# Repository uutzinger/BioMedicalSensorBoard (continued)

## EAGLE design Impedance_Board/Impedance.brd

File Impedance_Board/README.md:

# Tissue Impedance

IEC 60601 limits 100 µA maximum dc-leakage current through the body under normal conditions and 500 µA maximum under worst-case, single-fault conditions. An impedance circuit should not exceed that current.

## Analog Front Ends
### Analog Devices
- [AD5933 12-bit impedance converter ($18)](https://www.analog.com/en/products/ad5933.html) evaluation kit available ($68)
- [User Guide with reference schematics](https://www.analog.com/media/en/technical-documentation/user-guides/UG-364.pdf)

### Maxim AFE
- Biopotential
  - ECG (waveform)
  - R-R (heart rate)
- Bioimpedance
  - Resp (respiration)
  - GSR (galvanic skin response, stress level)
  - EDA (electro dermal activity)

- [Max 30001G ($10)](https://www.maximintegrated.com/en/products/analog/data-converters/analog-front-end-ics/MAX30001G.html) for Biopotential and Bioimpedance, evaluation kit available ($113)
- [Maxim 30009](https://www.maximintegrated.com/en/products/sensors/MAX30009.html) for Bioimpedance, evaluation kit available ($212)

### Summary of AFEs
| PART | Features             | Resolution | Remarks |
|---   |---                   |---         |---      |
| AD5933    | Single channel 3 wire | 12bit, 1Msps, 100kHz excitation| First Gen, 1024 point FFT, 1kOhm - 1MOhm
| AD5940/41 | 2 channel, 4 wire | 16bit, 800ksps, 200kHz | Impedance spectroscopy
| ADuC355   | 2 channel, 4 wire | 16bit, 800ksps, 200kHz | Impedance Spectroscopy, 26MHz ARM Cortex M3 MCU
| MAX30002  | single channel, BioZ, 2 or 4 wire | 17bit| 
| MAX30009  | single channel, BioZ, 2 or 4 wire | 16 kHz - 806 kHz |
| MAX30131/132/134 | 1-,2-,4- channel | 12 bit |
| MAX30001G | single channel, 2 or 4 wire | | Impedance and Potential (ECG)

## AD5933 for Bioimpedance

The AD5933 is a network analyzer IC that together with external circuitry can be used for bioimpedance measurements.

From [1] and [2], made with https://www.circuit-diagram.org/editor

### AD5933 Evaluation Board

The evaluation board from Analog Devices includes the reference design describing an analog front end to measure low impedances.

On the excitation side it has a passive high pass filter with $R_{HP}$, $C_{HP}$ and an OpAmp buffer.

On the measurement side it has an amplifier with $V_{DD}/2$ on the positive input and feedback resistor RFB.

The input to the AD5933 has $R_{AD_{IN}}$ of 20K as well as a $R_{AD_{FB}}$ of 20K.

### USING AD5933 for Bioimpedance Measurements

Munoz et al [2] describe their implementation in a 2022 paper. Several other web publications exist using that design.

For bioimpedance measurements the following analog front end elements should be used: a high-pass filter (HPF), a voltage-to-current converter (VCC), and an instrumentation amplifier (INA).

The HPF is a first order system composed of a 100 kΩ resistor and a 10 nF capacitor to remove the DC components of $V_{out}$. $f_c = 1 / (2 \pi R C)$ resulting in 160Hz. 

The HPF output is connected to VCC, which consists of an operational amplifier and two resistors. The current injected into the tissue should not exceed 10 uA. 

$R_{VCC current} = 1 kΩ$ (This will exceed 10 µA!)

$R_{VCC_{protect}} = 10 kΩ$

Because the impedance is supposed to vary from tens to hundreds of ohms, 

$R_{feedback} = 10 kΩ$ 

ensures that current flows mainly through $Z_{Load}$, which is connected in parallel to $R_{feedback}$.

The current through VCC is

$R_{VCC_{curent}} = (V_{out} - V_{ref}) / R_{VCC_{current}}$. 

Therefore the voltage over $Z_{load}$ is

$V_{Z_{load}} = -(V_{out} - V_{ref}) / R_{VCC_{current}} * Z_{load}$.

The unity gain instrumentation amplifier receives, through its non-inverting input, the voltages on the electrodes connected to $Z_{load}$. Since the ADC converter of the AD5933 is unipolar, a potential ($V_{ref}$) is added as reference voltage to the instrumentation amplifier. The output of the INA is 

$V_{INA} =  V_{load} + V_{ref}

The current through $R_{AD_{IN}}$ is:

$(V_{INA} - V_{ref})/R_{AD_{IN}}$

The output of the internal OpAmp in the AD5933 is 

$I_{RFB} * R_{AD_{FB}}$

Therefore 

$V_{AD5933} = (V_{INA} - V_{ref})/R_{AD{IN}} * R_{AD_{FB}}$.

The DSP of the AD5933 calculates the real and imaginary parts of $Z_{load}$, which are read through an inter-integrated circuit (I2C) protocol by a micro controller.

### External Electrical Components for AD5933

A list of designs using the AD5933 used the following values for resistors and capacitors:

| Design        | $C_{HP}$ | $R_{HP}$ | $RFB$ | $R_{VCC_{current}}$ | $R_{VCC_{protect}}$ | $R_{INA_{GAIN}}$ | $R_{REFGEN}$ | $R_{AD_{IN}}$ | $R_{AD_{FB}}$ | $VCC +$
|---            |---   |---    |---   |---            |---              |---            |---       |---      |---      |---
| Eval [1]      | 47nF | 49.9k | 200k | N.A.          | N.A.            | N.A.          | 49.9k    | 20k     | 20k     |
| Datasheet [3] | 47nF | N.S.  | N.S. | N.A.          | N.A.            | N.A.          | N.S.     | 20k     | 20k     |
| Munoz [2]     | 10nF | 100k  | N.A. | 1k            | 10k             | Gain=1        | 1k       | 1k      | 1k      | GND
| Instru Bio [4]| 10nF |  10k  | N.A. | 1k            |  1k             | Gain=10,5.5k  | VDD/2    | 1k      | 1k      | GND
| Instru BIA [5]| 10nF | 100k  | N.A. | 1M            |  1M             | Gain=1.5,100k | VDD/2    | 1k      | 1k      | GND
| Instru BIA [6]| 10nF | 100k  | N.A. | 285k          |  1M             |               | VDD/2    |         |         | VDD/2
| Instru Thor[7]| 1.2nF|  10k  | N.A. | 1M            |  1M             | Gain=1.5,100k | 1k       | 1k      | 1k      | GND
| Instru Thor[8]| 100nF|  20k  | N.A. | 100k          |  10k            | Gain=1.5,100k | 3.2/1k   | 1k      | 1k      | GND
| UA 2023       | 10nF | 100k  | N.A. |  82k          |  82k            | Gain=51,1k    | 20k      | 20k     | 20k     | VDD/2
| UA 2024       | 10nF | 100k  | 200k | 265k          |   1k            | Gain=51,1k    | 10k      | 20k     | 20k     | VDD/2

Common active components used for AD5933 biomimpedance:
- Network Analyzer AD5933
- Operation Amplifier(s) AD8608 or AD8606 or AD8605
- Instrumentation Amplifier INA826AID

#### High Pass
- $1 / (2 \pi R C)$, should attenuate 50 and 60Hz, need 200Hz..xxkHz
- 10nF, 100k fc=160Hz

#### $R_{current}$ and $R_{protect}$
- Input into VCC is at 1.65V offset with 1V amplitude. With $I_{CC} <10uA$ and $V_{CC} = 2.65V$ and $R_{VCC_{current}}$ will need to be 265kΩ.
- Setting of Range 1 in AD5933 is 1V if operating at 3.3V., for $10 \mu A$ we need 110kΩ for $R_{VCC_{current}}$.
- Analog Devices: "Bio-Impedance Circuit Design for Body Worn Systems"

#### $R_{Gain}$ 
- $G = 1 + (49.4k/R_{Gain})$
- With $R_{INA_{GAIN}}$  = 1kΩ the gain will be $G=51$

### Impedance Estimation

Formula to compute impedance from measurements: Description to be completed (check evaluation board and Instructables, also search PubMed).

### References

For general reading: [Analog Devices: Bio-Impedance Circuit Design for Body Worn Systems"](https://www.analog.com/en/resources/analog-dialogue/articles/bioimpedance-circuit-design-challenges.html)

1) [Analog Devices AD5933 Evaluation Board, User Guide](https://www.analog.com/media/en/technical-documentation/user-guides/UG-364.pdf)
2) [Munoz et al](https://doi.org/10.1016%2Fj.ohx.2022.e00274)
3) [AD5933 Datasheet](https://www.analog.com/media/en/technical-documentation/data-sheets/AD5933.pdf)
4) [Instructables Body Composition](https://www.instructables.com/Determining-Body-Composition-using-Arduino)
5) [Instructables BIA 1](https://www.instructables.com/Body-Composition-using-BIA/)
6) [Instructables BIA 2](https://www.instructables.com/Bio-Impedance-Analysis-BIA-With-the-AD5933/)
7) [Instructables Thor 1](https://www.instructables.com/Thoracic-Impedance-1/)
8) [Instructables THor 2](https://www.instructables.com/Thoracic-Impedance/)
9) [IEEE Tutorial](https://ieeexplore.ieee.org/document/9529213)
10) [Uwe Pliquett, Andreas Barthel, 2012 J. Phys.: Conf. Ser. 407 012019](https://iopscience.iop.org/article/10.1088/1742-6596/407/1/012019)
10) [Paco Bogonez-Franco et al, 2014, Problems encountered during inappropriate use of commercial bioimpedance devices in novel applications, 7 th International Workshop on Impedance Spectroscopy 2014](https://www.researchgate.net/publication/269571754_Problems_encountered_during_inappropriate_use_of_commercial_bioimpedance_devices_in_novel_applications)
12) [J Ferreira et al 2010 J. Phys.: Conf. Ser. 224 012011](https://iopscience.iop.org/article/10.1088/1742-6596/224/1/012011/pdf)

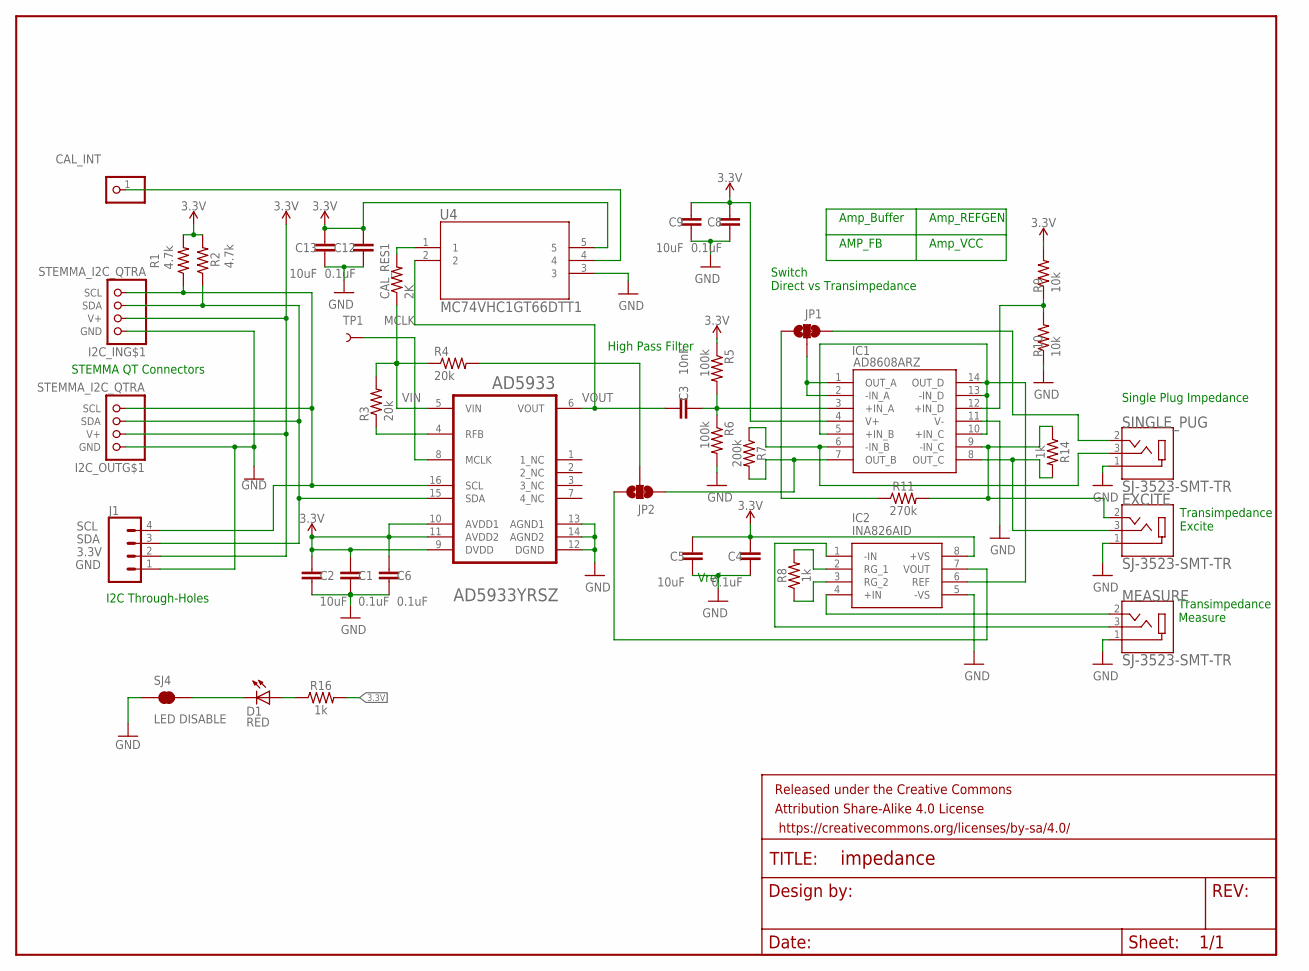
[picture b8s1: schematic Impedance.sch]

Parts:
AD5933: ANALOG_DEVICES_AD5933YRSZANALOG_DEVICES_AD5933YRS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; ANALOG_DEVICES_AD5933YRSZ_0
C1, C4, C6, C8, C12: 0.1uF; 0603
C2, C5, C9, C13: 10uF; 0603
C3: 10nF; 0603
CAL_INT: PINHD-1X1; 1X01
CAL_RES1: 2K; R0603
D1: RED; LED-0603
EXCITE: SJ-3523-SMT-TR; CUI_SJ-3523-SMT-TR
FRAME1: FRAME-LETTERNO_PACKAGE; DUMMY
I2C_IN, I2C_OUT: STEMMA_I2C_QTRA; JST_SH4_RA
IC1: AD8608ARZ; SOIC127P600X175-14N
IC2: INA826AID; SOIC127P600X175-8N
J1: CONN_04; 1X04
JP1, JP2: JUMPER-SMT_3_1-NC_TRACE_NO-SILK; SMT-JUMPER_3_1-NC_TRACE_NO-SILK
MEASURE: SJ-3523-SMT-TR; CUI_SJ-3523-SMT-TR
R1, R2: 4.7k; 0603
R3, R4: 20k; 0603
R5, R6: 100k; 0603
R7: 200k; 0603
R8, R14, R16: 1k; 0603
R9, R10: 10k; 0603
R11: 270k; 0603
SINGLE_PUG: SJ-3523-SMT-TR; CUI_SJ-3523-SMT-TR
SJ4: LED DISABLE; SMT-JUMPER_2_NC_TRACE_SILK
TP1: TEST-POINT3X5; PAD.03X.05
U4: MC74VHC1GT66DTT1; TSOP5_1P65X3P15_ONS

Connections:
3.3V: AD5933.9 (DVDD), AD5933.10 (AVDD1), AD5933.11 (AVDD2), C1.1, C2.1, C4.1, C5.1, C6.1, C8.1, C9.1, C12.1, C13.1, I2C_IN.2 (V+), I2C_OUT.2 (V+), IC1.4 (V+), IC2.8 (+VS), J1.2, R1.2, R2.2, R5.1, R9.2, R16.2, U4.5
GND: AD5933.12 (DGND), AD5933.13 (AGND1), AD5933.14 (AGND2), C1.2, C2.2, C4.2, C5.2, C6.2, C8.2, C9.2, C12.2, C13.2, EXCITE.1, I2C_IN.1 (GND), I2C_OUT.1 (GND), IC1.11 (V-), IC2.5 (-VS), J1.1, MEASURE.1, R6.2, R10.1, SINGLE_PUG.1, SJ4.1, U4.3
MCLK: AD5933.8 (MCLK), TP1.P$1
unnamed: IC1.6 (-IN_B), R7.1, SINGLE_PUG.3
unnamed: CAL_INT.1, U4.4
unnamed: IC1.7 (OUT_B), JP2.3, R7.2
unnamed: JP2.2, R4.2
unnamed: AD5933.4 (RFB), R3.1
unnamed: C3.2, IC1.3 (+IN_A), R5.2, R6.1
unnamed: JP1.1, R11.1
unnamed: IC1.1 (OUT_A), IC1.2 (-IN_A), JP1.2
unnamed: IC2.7 (VOUT), JP2.1
unnamed: IC1.12 (+IN_D), R9.1, R10.2
unnamed: JP1.3, SINGLE_PUG.2
unnamed: IC1.5 (+IN_B), IC1.10 (+IN_C), IC1.13 (-IN_D), IC1.14 (OUT_D), IC2.6 (REF)
unnamed: EXCITE.2, IC1.9 (-IN_C), R11.2, R14.1
unnamed: IC2.4 (+IN), MEASURE.2
unnamed: IC2.1 (-IN), MEASURE.3
unnamed: IC2.2 (RG_1), R8.2
unnamed: IC2.3 (RG_2), R8.1
unnamed: CAL_RES1.2, U4.1
unnamed: EXCITE.3, IC1.8 (OUT_C), R14.2
unnamed: D1.A, R16.1
unnamed: D1.C, SJ4.2
SCL: AD5933.16 (SCL), I2C_IN.4 (SCL), I2C_OUT.4 (SCL), J1.4, R1.1
SDA: AD5933.15 (SDA), I2C_IN.3 (SDA), I2C_OUT.3 (SDA), J1.3, R2.1
VIN: AD5933.5 (VIN), CAL_RES1.1, R3.2, R4.1
VOUT: AD5933.6 (VOUT), C3.1, U4.2

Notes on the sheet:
High Pass Filter
Vref
Transimpedance Measure
Transimpedance Excite
Single Plug Impedance
STEMMA QT Connectors
I2C Through-Holes
Switch Direct vs Transimpedance
Amp_VCC
Amp_REFGEN
Amp_Buffer
AMP_FB

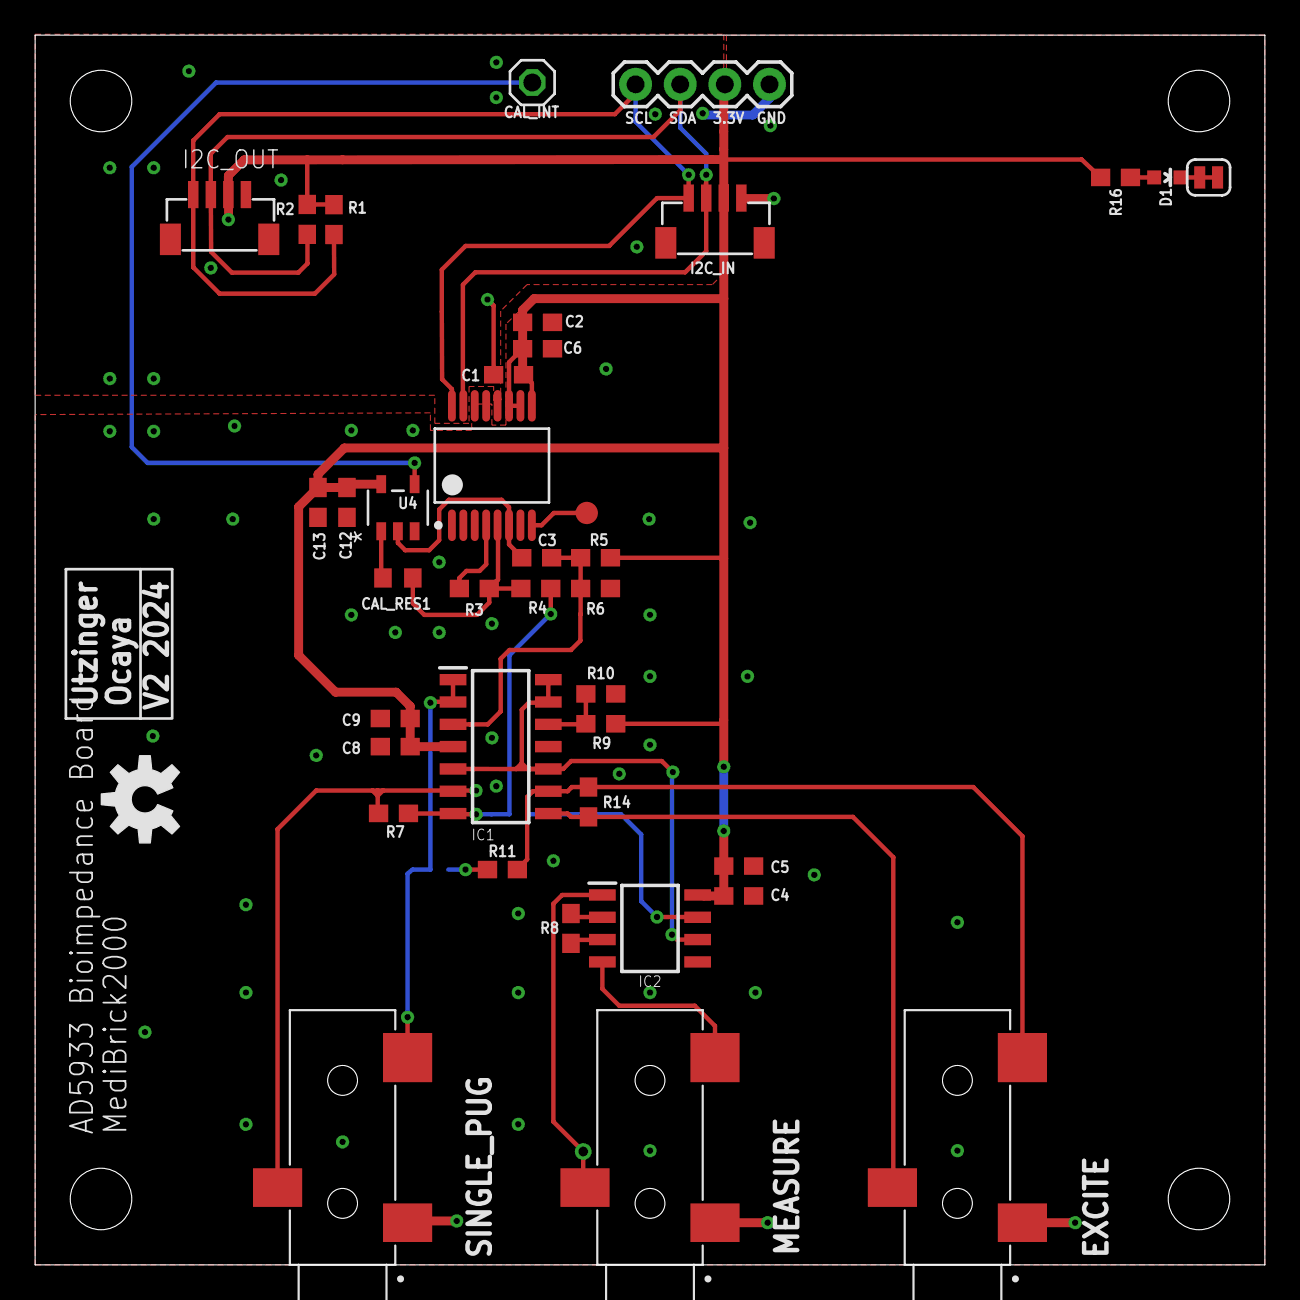
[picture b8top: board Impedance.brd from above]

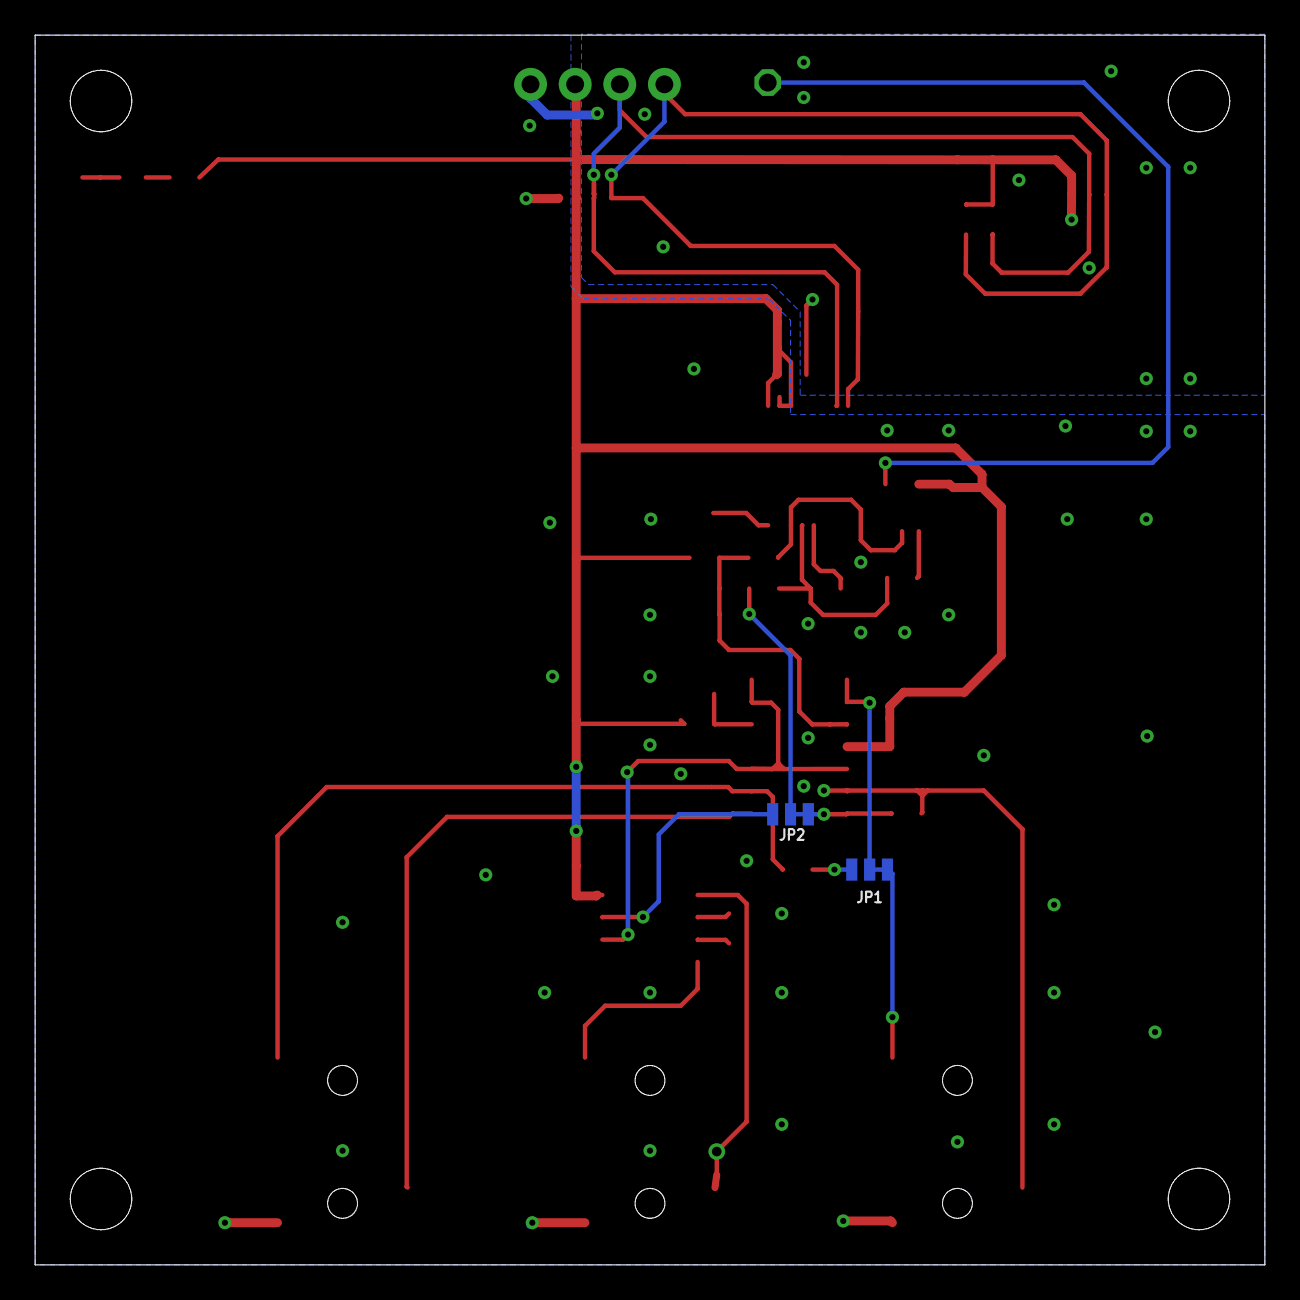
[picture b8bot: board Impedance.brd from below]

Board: 2 copper layers, 70.0 x 70.0 mm, 42 parts (2 on the bottom side), 28 nets.

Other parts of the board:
U$2: OSHW-LOGO-M

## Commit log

2023-09-11 Create ECG
2023-09-11 Rename ECG to ECG.md
2023-09-11 Rename Sound.md to sound.md
2023-09-15 Thermistor Board
2023-09-16 Thermistor Board
    Thermistor board with BOM and GERBER files for manufacturing and assembly
2023-09-16 Directory name
2023-09-16 Documentation updates
2023-09-17 Update graphics
2023-09-17 Minor Updates LTC board
    Silkscreen
    Updates to via positions
2023-09-17 Skeleton for other boards
2023-10-25 Routing Impedance Board
2023-10-25 Impedance Circuit Explanation
2023-11-06 ESP32 Continuous ADC
2023-12-10 Python Serial Helper
    First Release of Python Based Serial Interface emulating Arduino IDE.
2023-12-11 Debugging of most functions
2024-01-22 Example Arduino Code
    First release of example Arduino Code
    Updates to Impedance general design
2024-02-08 Board Updates, Reorganize
2024-02-08 Cleanup
2024-02-10 Updated SPO2
    Crosse Checked with Data Sheet and Evaluation Board
    Added 10Ohm resistors in data lines
    Adjusted capacitors
2024-02-12 Impedance
    Minor change SPO2
2024-02-12 Impedance Vref fic
    INA needs Vref
2024-02-14 Impedance update
2024-02-14 Merging project and Impedance update (description)
2024-02-15 Background and Documentation
2024-02-15 Some documentation polishing
2024-02-15 MAX30001G
2024-02-15 Typo
2024-02-22 BOM MAX30001G and board updates
2024-02-23 CAM Impedance_Potential Board
2024-02-24 3 Channel Analog Temp
2024-02-24 Sound updates
2024-02-27 Temp
    3 Channel board
    Writeup update
2024-02-29 Sound Board
    Sound Board with ES8388 by PCBArtists
    Cleanup
2024-02-29 math fix
2024-03-01 Updated Sound Board
2024-03-05 Cleanup, organization and updates
2024-03-16 Board Updates
    All LEDs at same location
    Separated analog and digital ground
    Updated impedance components
2024-03-24 Board Updates
    Separated analog and digital ground
    Updated routing
    Updated silk labeling
    Sound board with ES8388 included
    Impedance and ECG board
    Working on IMU board
2024-03-30 Air quality
2024-04-02 Air Quality at 3.3V with 5V boost for PM sensor
2024-04-21 IMU board
    Completed IMU board design
    Updated designs with ground via close to any other via.
2024-04-21 IMU description
2024-05-02 Production Updates
2024-05-02 Sound Board Updates
2024-07-02 Merging Production Status to Github, Obtaining senior design files
2024-07-15 MAX3001 updates
    MAX3001 still much more to do
    Drivers for other chips obtained from manufacturer and other sources
2024-08-08 Passed Tests
    Many sensors passed testing,
    Many library updates
2024-08-11 Docu Updates
2024-08-14 Mechanical Designs, Documentation
2024-10-18 Major Update
2024-10-19 Updated documentation
2024-10-19 PCBWay quotations
2024-10-20 Update issue templates
2024-10-20 BMES 2024 Poster
2024-10-20 picture update
2024-10-20 Concept Drawing Update
